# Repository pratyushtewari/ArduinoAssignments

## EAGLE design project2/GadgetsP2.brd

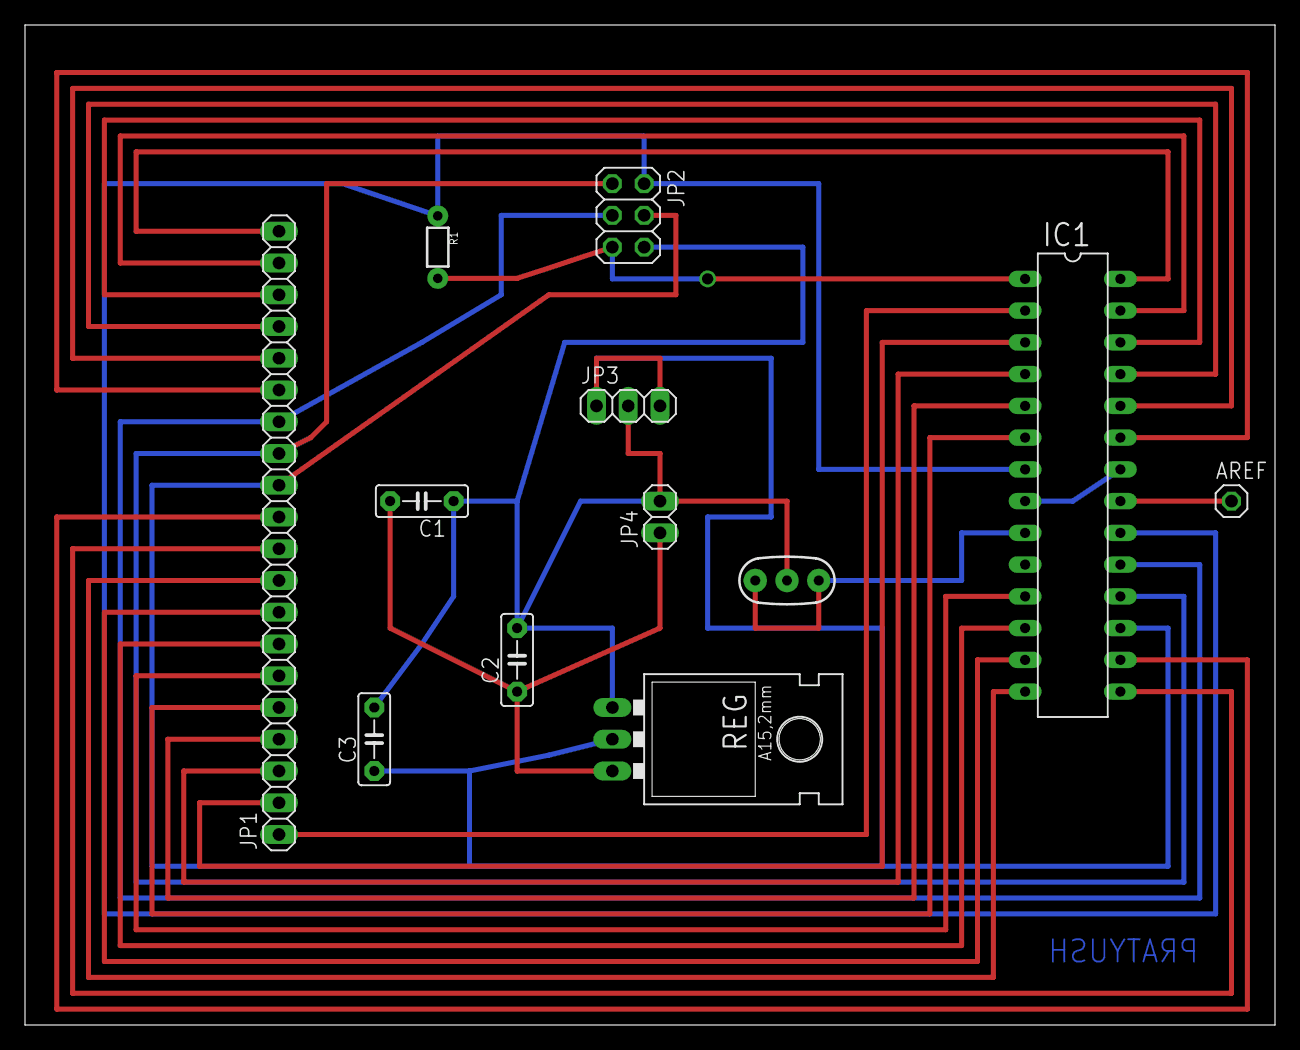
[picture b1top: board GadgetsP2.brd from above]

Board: 2 copper layers, 100.0 x 80.0 mm, 12 parts (0 on the bottom side), 28 nets.

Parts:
AREF: 1X01
C1, C2, C3: C5B2.5
IC1: MEGA8-P; DIL28-3
JP1: 1X20
JP2: 2X03
JP3: 1X03
JP4: 1X02
R1: 1/6W-RES
REG: 78XXL
Y1: RESONATOR-PTH

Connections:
+5V: IC1.7, IC1.20, JP2.2, R1.1
A0: IC1.23, JP1.15
A1: IC1.24, JP1.16
A2: IC1.25, JP1.17
A3: IC1.26, JP1.18
A4: IC1.27, JP1.19
A5: IC1.28, JP1.20
D0: IC1.2, JP1.1
D1: IC1.3, JP1.2
D2: IC1.4, JP1.3
D3: IC1.5, JP1.4
D4: IC1.6, JP1.5
D5: IC1.11, JP1.6
D6: IC1.12, JP1.7
D7: IC1.13, JP1.8
D8: IC1.14, JP1.9
D9: IC1.15, JP1.10
D10: IC1.16, JP1.11
D11: IC1.17, JP1.12, JP2.4
D12: IC1.18, JP1.13, JP2.1
D13: IC1.19, JP1.14, JP2.3
GND: C1.1, C2.2, C3.2, JP2.6, JP3.2, JP4.2, REG.IN, Y1.2
unnamed: IC1.9, Y1.1, Y1.3
unnamed: AREF.1, IC1.21
RESET: IC1.1, JP2.5, R1.2
S$1: C1.2, C2.1, JP4.1, REG.OUT
S$2: IC1.8, IC1.22
V+: C3.1, JP3.1, JP3.3, REG.GND

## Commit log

2014-02-15 Added Files
2014-02-22 Added death and animation reset
2014-02-22 Fixed bug for new points
2014-02-22 Added levels
2014-02-27 adding comments
2014-05-09 final

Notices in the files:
parts and their libraries:
SparkFun-FreqCtrl: Licensing: Creative Commons ShareAlike 4.0 International - https://creativecommons.org/licenses/by-sa/4.0
